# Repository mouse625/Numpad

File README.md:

# Numpad

>   self-explanatory, a custom macropad functioning as a numpad.

## Description

Numpad is a [Macropad](https://www.google.com/search?q=Macropad), a custom sort of mini-keyboard usually designed for faster inputting of hardcoded shortcuts/strings or specific functions. However, this macropad is made as a [Numpad](https://www.google.com/search?q=Numpad) accessory for more efficient inputting of numbers.

This project is made possible by [Hackpad](https://www.google.com/search?q=Hackpad+for+Hack+Club), a YSWS (you ship we ship) event on making a custom Macropad run by [Hack Club](https://www.google.com/search?q=Hack+Club).

## Features

### Physical Features

- 10 keys numbered 0 through 9
- 3D printed case
- Custom PCB in a [Sandwich Mount](https://www.google.com/search?q=Sandwich+Mount)

### Repository Features

- assets
    - models
    - renderings
- source files
    - kicad design files
        - project file
        - schematics
        - layouts
    - cad mockup
        - pcb
            - components
                - keyswitches
                - keycaps
                - diodes
                - xiao
            - the actual pcb
        - case
            - main body
            - top plate
        - cable (useful for designing an appropriate opening for power)
    - qmk firmware
        - keyboard.json
        - keymap.c
- production
    - cad
        - case
            - bottom section
            - top section
            - new top section (made in a pinch for easier installing)
    - firmware
        - compiled uf2 file
    - pcb
        - compressed folder of the gerbers

## Renderings

>   we all know you love them.

<details>
  <summary></summary>
  hidden in the code of this document (right below this details tag) is an AI-generated (yes, I know) image row alignment guide so I don't forget how to...align images.
</details>

<!--
# Image Row Alignment Guide

### Core Mathematical Formulation

Given a row containing $n$ distinct images, let each image $i \in \{1, 2, \dots, n\}$ possess an intrinsic width $W_i \in \mathbb{R}^+$ and an intrinsic height $H_i \in \mathbb{R}^+$ measured in pixels.

#### 1. Image Aspect Ratio ($R_i$)
The dimensional aspect ratio for an individual image element $i$ is defined as:
$$R_i = \frac{W_i}{H_i}$$

#### 2. Combined Row Share ($\mathcal{S}$)
The aggregate dimensional proportion of the horizontal row sequence is the summation of all individual component ratios:
$$\mathcal{S} = \sum_{i=1}^{n} R_i$$

#### 3. Normalized Image Width Percentage ($P_i$)
To constrain the horizontal sequence to exactly 100% of the parent viewport width container while enforcing a uniform visual height baseline across the row, the relative percentage allocation $P_i$ for each image $i$ is formulated as:
$$P_i = \left( \frac{R_i}{\mathcal{S}} \right) \times 100 = \left( \frac{\frac{W_i}{H_i}}{\sum_{j=1}^{n} \frac{W_j}{H_j}} \right) \times 100$$

---

### Code Architecture Templates

#### Single-Row Configuration
```html

```

#### Multi-Row Compact Configuration
```html
<p align="center">
  
  <br>
  
</p>
```
-->

### PCB

### CAD

>   one assembly image (the others are mostly for eye-candy).

<p align="center">
  
  <br>
  
</p>

### Photos

>   not exactly orthodox "renderings".

## Assembly

### BoM

>   the parts.

- 1x custom-built `PCB`
- 1x unsoldered `Seeed XIAO RP2040`
- 10x through-hole `1N4148 Diodes`
- 10x `MX-Style switches`
- 10x white blank `DSA Keycaps`
- 4x `M3x16mm Screws`
- 1x 3D-printed `Case`
    - 1x 3D-printed `Bottom Section`
    - 1x 3D-printed `Top Section`

>   the tools (not really part of the BoM but whatever).

- 1x `Soldering Iron`
- 1x roll of (with a decent amount left) `Solder`
- 1x tool for clipping pins (either/or)
  - 1x (optional) pair of `Wirecutters`
  - 1x (optional) pair of `Scissors`
- 1x tool for screwing the...screws during assembly (either/or)
  - 1x (optional) hex-head `Screwdriver`
  - 1x (optional) `hex key` preferable without an obligatory hex
- 1x `Flashing Setup` for...flashing
  - 1x USB-C `Cable` (for power too)
  - 1x functioning `Computer`
- 1x (optional) functioning `3D Printer`
- 1x (optional) full-fledged `Factory` for making PCBs
  - 1x `CNC Router`
  - 1x `Laser Plotter`
  - 1x `Chemical Etcher`
  - 1x `Plating System`
  - 1x `Silkscreen Printer`
- 1x functioning [`Encephalon`](https://www.google.com/search?q=Encephalon)

### Instructions

<ol>
  <li>After receiving your parts, including the <code>PCB</code>, <code>components</code> and <code>case</code>, you'll need to have/obtain access to a <code>soldering iron</code> and some <code>solder</code>, a pair of <code>wire cutters</code> or <code>scissors</code>, a functioning <code>computer</code> and a <strong>USB-C</strong> <code>cable</code>.</li>
  <li>First and foremost, the <strong>firmware</strong> needs to be loaded onto the <code>XIAO</code>.
    <ol type="a">
      <li>This is done by plugging the USB-C <code>cable</code> into the <code>XIAO</code>'s <strong>port</strong>.</li>
      <li>The physical <strong>boot button</strong> on the <code>XIAO</code> can then be <strong>held</strong> while plugging the other side of the <code>cable</code> into the <code>computer</code> to enter <strong>bootloader mode</strong>.</li>
      <li>The <code>XIAO</code> should appear as a <strong>removable flash drive</strong> into which the <strong>.uf2 compiled firmware</strong> can be <strong>dragged and dropped</strong>.</li>
      <li>The <code>XIAO</code> can safely be unplugged and is ready to solder.</li>
    </ol>
  </li>
  <li>The first things to solder are your <code>diodes</code>.
    <ol type="a">
      <li>Align the <strong>stripes</strong> on each one of the <code>diodes</code> with the <strong>stripes</strong> on the <code>PCB</code> indicating the direction of the <code>diodes</code>.</li>
      <li>The <code>diodes</code> can then simply be soldered onto the <code>PCB</code> with the <code>soldering iron</code> while slowly feeding <code>solder</code>.</li>
      <li>Lastly, the <strong>legs</strong> need to be snipped off with the <code>wire cutters</code> or <code>scissors</code> (this is highly recommended).</li>
    </ol>
  </li>
  <li>The next step is to solder your flashed <code>XIAO</code> onto the <code>PCB</code>'s <strong>underside</strong>. This should be constantly cross-referenced with the <strong>CAD model</strong> to avoid any desoldering.</li>
  <li>After this, the <code>keyswitches</code> need to be installed.
    <ol type="a">
      <li>BEFORE any soldering takes place, they need to be clipped onto the <code>PCB</code>. The <code>case plate</code> is REQUIRED to be <strong>between</strong> the <code>keyswitches</code> and the <code>PCB</code> during this step.</li>
      <li>Following the previous substep, the <code>keyswitches</code> can now safely be soldered.</li>
    </ol>
  </li>
  <li>The <code>case plate</code> and <code>main body</code> can now be aligned with the <code>PCB</code> (sandwiched in the middle). A <code>hex key</code> or <strong>hex-head</strong> <code>screwdriver</code> can then be used to screw 4 <strong>M3x16mm</strong> <code>screws</code> into their respective locations.</li>
  <li>Lastly, the <code>keycaps</code> can then be popped into place on your newly-assembled <code>numpad</code> (sadly, it doesn't work magically, so it wasn't really "lastly").</li>
  <li>The USB-C cable can now be plugged into the <code>numpad</code> and your <code>computer</code>, which acts as <strong>power</strong>.</li>
</ol>

## Contributions

Do you have any suggestions, fixes, or extensions? If so, you can submit a pull request on this [Repository](https://github.com/MouseMouse625/Numpad).

## Credits

Credits to:
- [`HCB`](https://hackclub.com) for hosting this whole thing
    - [`Stardance`](https://stardance.hackclub.com) for running an actual summer event
        - [`Hackpad`](https://hackpad.hackclub.com) for inspiration on this specific project
            - [`0xmanidev`](https://github.com/0xmanidev) for their schematics made for Spacepad as a reference on [Matrix Wiring](https://www.google.com/search?q=Matrix+Wiring)
            - [`CodeCraftPlugin`](https://github.com/CodeCraftPlugin) for making Stream Deck act as a reference for finding the correct DSA keycap models (turns out it was in the parts list that I wrote, so...yeah)
            - [`cheyao`](https://github.com/cheyao) for creating the guides
- [`GrabCAD`](https://grabcad.com) for their open-source CAD models of various parts
    - [`kevin.yu-7`](https://grabcad.com/kevin.yu-7) for their models of the Cherry MX Keyswitches
    - [`mirac.gulgonul-1`](https://grabcad.com/mirac.gulgonul-1) for their model of the Seeed Studio XIAO RP2040
    - [`chris.barnado-1`](https://grabcad.com/chris.barnado-1) for their model of the flexed USB-C Cable
    - [`zim.cad-1`](https://grabcad.com/zim.cad-1) for their models of the blank white DSA Keycaps
- [`McMaster-Carr`](https://www.mcmaster.com) for their huge library of various models, most importantly the M3x16 screws
- [`Shapr3D`](https://www.shapr3d.com), [`VSCode`](https://code.visualstudio.com) and [`KiCad`](https://www.kicad.org) for making the CAD section of all of this possible
- [`Google`](https://www.google.com) for acting as a universal search engine for all of my dumb queries

## License

This project uses the MIT License stating that the project is open source and free for anyone to use or develop. For more info, navigate to the [LICENSE.md](LICENSE.md) file.

---

Copyright © 2025 Numpad

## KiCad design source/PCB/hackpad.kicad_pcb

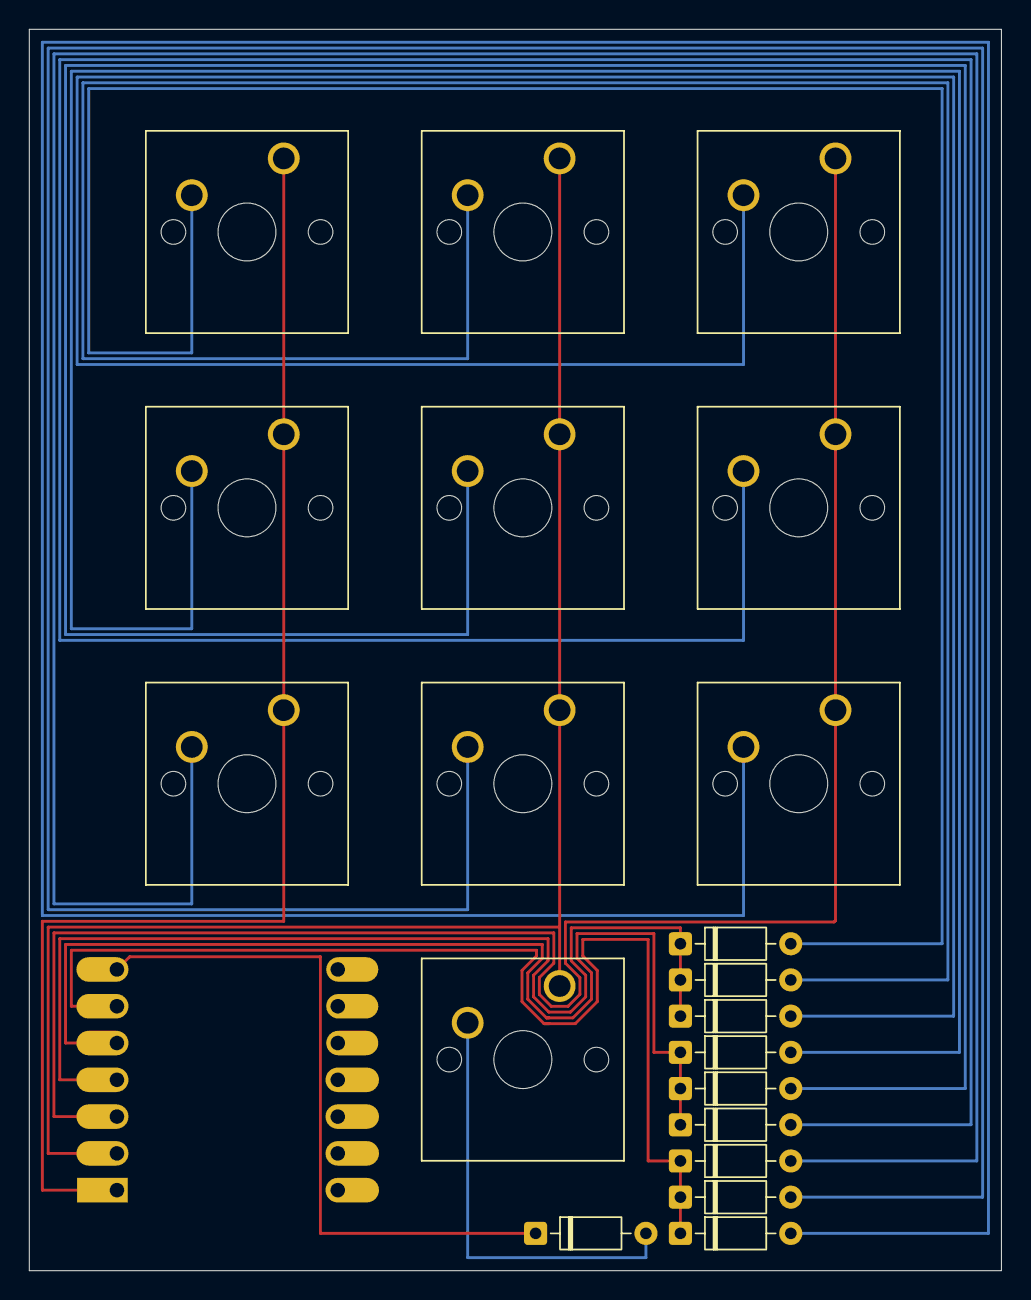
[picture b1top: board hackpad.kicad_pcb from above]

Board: 2 copper layers, 67.1 x 85.7 mm, 21 parts (1 on the bottom side), 17 nets.

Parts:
D0, D1, D2, D3, D4, D5, D6, D7, D8, D9: 1N4148; D_DO-35_SOD27_P7.62mm_Horizontal
SW0, SW1, SW2, SW3, SW4, SW5, SW6, SW7, SW8, SW9: SW_Push_45deg; SW_Cherry_MX_1.00u_PCB
U1: MOUDLE-SEEEDUINO-XIAO; XIAO-Generic-Hybrid-14P-2.54-21X17.8MM

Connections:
COL1: SW1.1, SW4.1, SW7.1, U1.1 (PA02_A0_D0)
COL2: SW0.1, SW2.1, SW5.1, SW8.1, U1.2 (PA4_A1_D1)
COL3: SW3.1, SW6.1, SW9.1, U1.3 (PA10_A2_D2)
unnamed: D0.2 (A), SW0.2
unnamed: D1.2 (A), SW1.2
unnamed: D2.2 (A), SW2.2
unnamed: D3.2 (A), SW3.2
unnamed: D4.2 (A), SW4.2
unnamed: D5.2 (A), SW5.2
unnamed: D6.2 (A), SW6.2
unnamed: D7.2 (A), SW7.2
unnamed: D8.2 (A), SW8.2
unnamed: D9.2 (A), SW9.2
ROW1: D1.1 (K), D2.1 (K), D3.1 (K), U1.4 (PA11_A3_D3)
ROW2: D4.1 (K), D5.1 (K), D6.1 (K), U1.5 (PA8_A4_D4_SDA)
ROW3: D7.1 (K), D8.1 (K), D9.1 (K), U1.6 (PA9_A5_D5_SCL)
ROW4: D0.1 (K), U1.7 (PB08_A6_D6_TX)
